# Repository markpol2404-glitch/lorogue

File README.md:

# lorogue
A small ESP32S3 enabled device, with LoRa connectivity.

This PCB/Schematic uses an Wio-S3 from SEEED Studio, a module that contains a LoRa module and a ESP32S3 MCU.

USB C connectivity along with an ESD protection.

Cool "minimalengineering" backdesign.

minimal_engineering on instagram

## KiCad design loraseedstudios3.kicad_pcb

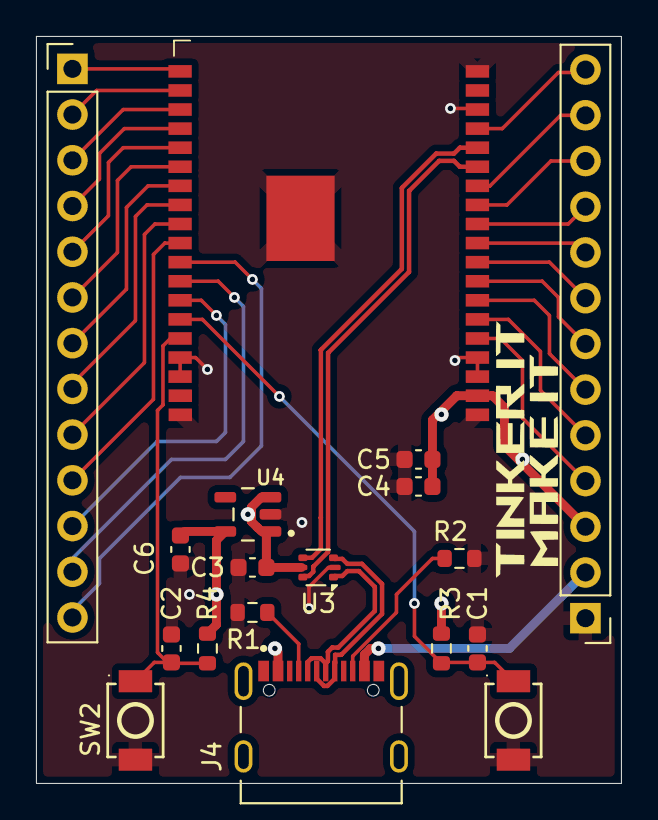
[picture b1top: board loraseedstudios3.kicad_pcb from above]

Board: 4 copper layers, 32.5 x 41.5 mm, 18 parts (0 on the bottom side), 34 nets.

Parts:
C1, C2, C6: 100n; C_0603_1608Metric
C3, C4: 1u; C_0603_1608Metric
C5: 10u; C_0603_1608Metric
J1, J2: Conn_01x13_Pin; PinHeader_1x13_P2.54mm_Vertical
J4: USB_C_Receptacle_USB2.0_16P; SHOUHAN_TYPE-C_16PIN_2MD__073_
R1, R2: 5.1k; R_0603_1608Metric
R3, R4: 10k; R_0603_1608Metric
SW1, SW2: SW_Push; C720477_SW-SMD_L3_9-W3_0-P4_45
U1: Wio-S3; Wio-S3 Wireless Module
U3: USBLC6-2P6; SOT-666
U4: TLV75733PDBVR; SOT95P280X145-5N

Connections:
+3.3V: C4.1, C5.1, C6.1, J2.3, R3.1, R4.1, U1.21 (VCC), U4.5 (OUT)
+5V: C3.1, J2.2, J4.A4 (VBUS), U3.5 (VBUS), U4.1 (IN), U4.3 (EN)
/DN: U1.33 (GPIO19/USB_DM), U3.6 (I/O1)
/DP: U1.34 (GPIO20/USB_DP), U3.4 (I/O2)
/IO1: J1.11, U1.13 (GPIO1)
/IO2: J1.12, U1.12 (GPIO2)
/IO3: J1.13, U1.11 (GPIO3)
/IO10: J2.5, U1.25 (GPIO10)
/IO11: J2.4, U1.24 (GPIO11)
/IO12: J2.6, U1.26 (GPIO12)
/IO13: J2.7, U1.27 (GPIO13)
/IO14: J2.8, U1.28 (GPIO14)
/IO15: J2.9, U1.29 (GPIO15)
/IO16: J2.10, U1.30 (GPIO16)
/IO17: J2.11, U1.31 (GPIO17)
/IO18: J2.12, U1.32 (GPIO18)
/IO38: J1.2, U1.2 (GPIO38)
/IO39: J1.3, U1.3 (GPIO39)
/IO40: J1.4, U1.4 (GPIO40)
/IO41: J1.5, U1.5 (GPIO41)
/IO42: J1.6, U1.6 (GPIO42)
/IO45: J1.9, U1.9 (GPIO45)
/IO46: J1.10, U1.10 (GPIO46)
/IO47: J1.1, U1.1 (GPIO47)
/IO48: J2.13, U1.35 (GPIO48)
/RX: J1.8, U1.8 (GPIO44/UART0_RX)
/TX: J1.7, U1.7 (GPIO43/UART0_TX)
/USBN: J4.A7 (D-), J4.B7 (D-), U3.1 (I/O1)
/USBP: J4.A6 (D+), J4.B6 (D+), U3.3 (I/O2)
GND: C1.1, C2.1, C3.2, C4.2, C5.2, C6.2, J2.1, R1.2, R2.2, SW1.1, SW2.1, U1.16 (GND), U1.17 (GND), U1.19 (GND), U1.20 (GND), U1.22 (GND), U1.23 (GND), U1.36 (GND), U1.38 (GND), U1.39 (GND), U3.2 (GND), U4.2 (GND)
unnamed: J4.A5 (CC1), R1.1
unnamed: J4.B5 (CC2), R2.1
unnamed: C1.2, R3.2, SW1.2, U1.14 (BOOT)
unnamed: C2.2, R4.2, SW2.2, U1.15 (RST)
